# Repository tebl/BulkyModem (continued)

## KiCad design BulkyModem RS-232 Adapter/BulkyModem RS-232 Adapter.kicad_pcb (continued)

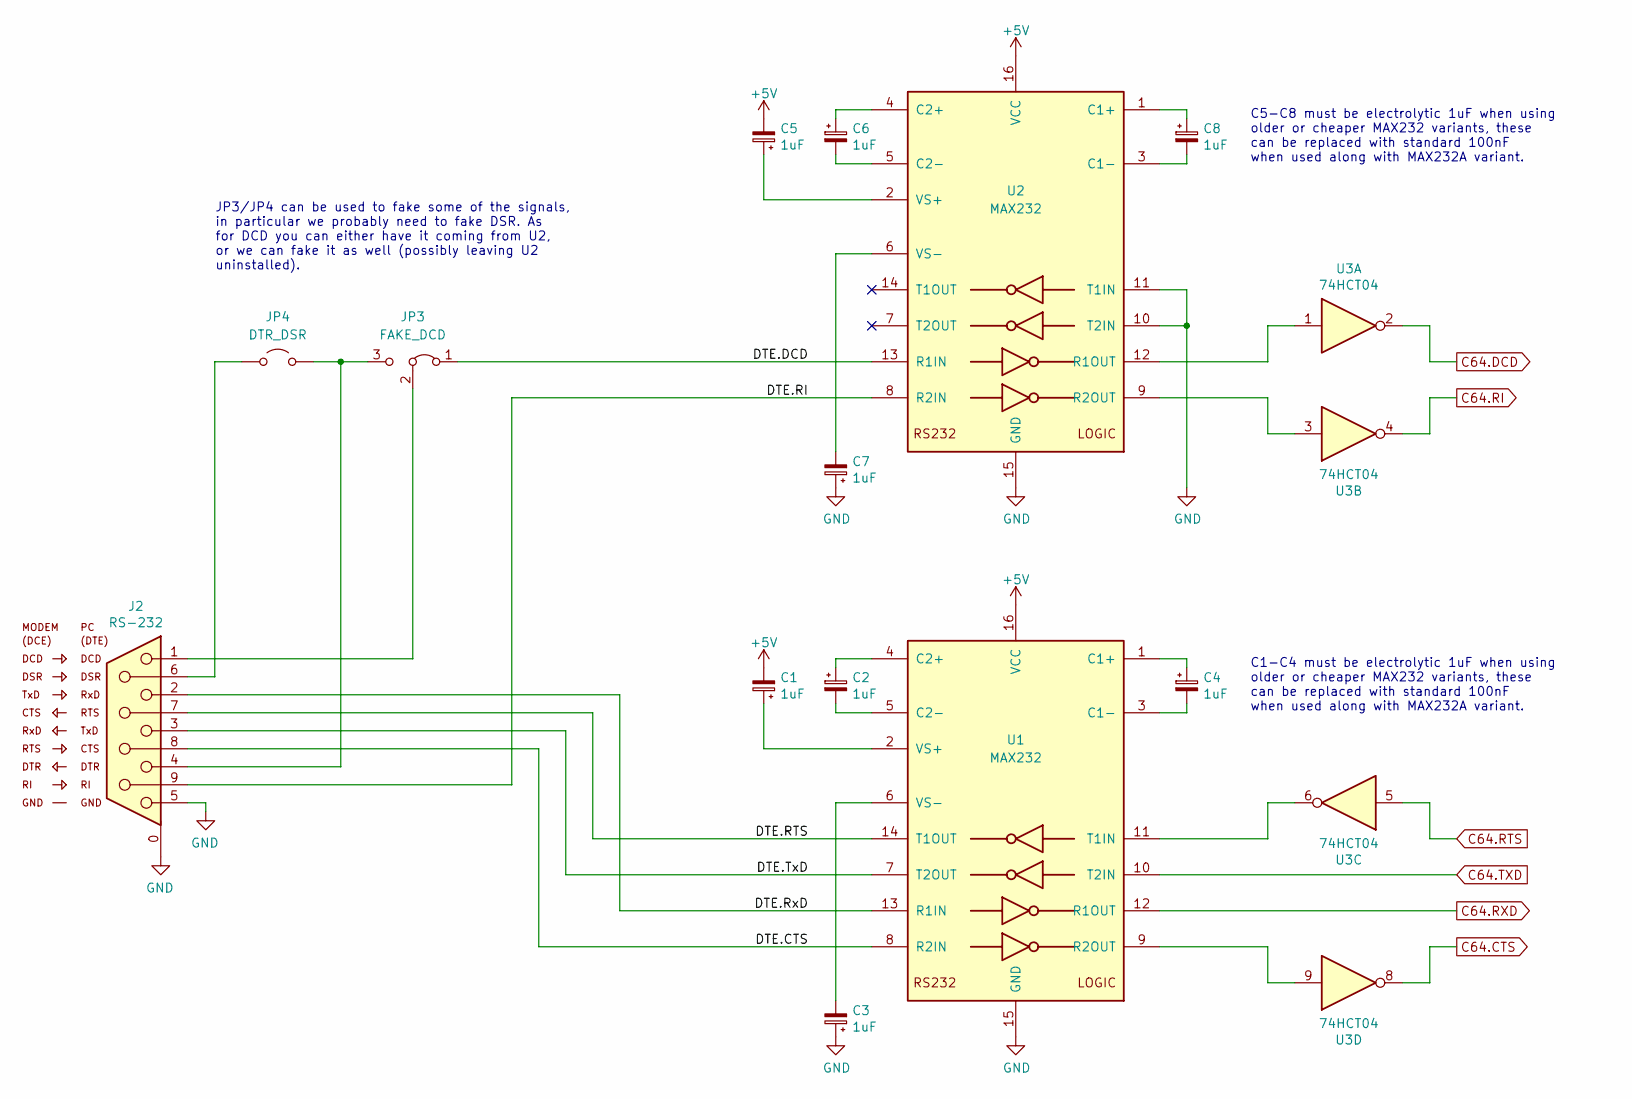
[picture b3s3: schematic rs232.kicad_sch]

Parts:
C1, C2, C3, C4, C5, C6, C7, C8: 1uF; CP_Radial_D4.0mm_P2.00mm_Custom
J2: RS-232; DSUB-9_Male_Horizontal_P2.77x2.84mm_EdgePinOffset7.70mm_Hou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
JP3: FAKE_DCD; PinHeader_1x03_P2.54mm_Vertical
JP4: DTR_DSR; PinHeader_1x02_P2.54mm_Vertical
U1, U2: MAX232; DIP-16_W7.62mm_Socket_LongPads
U3: 74HCT04; DIP-14_W7.62mm_Socket_LongPads

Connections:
+5V: C1.2, C5.2, U1.16 (VCC), U2.16 (VCC); also elsewhere on the board
/RS-232/DTE.CTS: J2.8, U1.8 (R2IN)
/RS-232/DTE.DCD: JP3.1 (A), U2.13 (R1IN)
/RS-232/DTE.RI: J2.9, U2.8 (R2IN)
/RS-232/DTE.RTS: J2.7, U1.14 (T1OUT)
/RS-232/DTE.RxD: J2.2, U1.13 (R1IN)
/RS-232/DTE.TxD: J2.3, U1.7 (T2OUT)
C64.CTS: U3.8; also elsewhere on the board
C64.DCD: U3.2; also elsewhere on the board
C64.RI: U3.4; also elsewhere on the board
C64.RTS: U3.5; also elsewhere on the board
C64.RXD: U1.12 (R1OUT); also elsewhere on the board
C64.TXD: U1.10 (T2IN); also elsewhere on the board
GND: C3.1, C7.1, J2.0 (S), J2.5, U1.15 (GND), U2.10 (T2IN), U2.11 (T1IN), U2.15 (GND); also elsewhere on the board
unnamed: J2.4, JP3.3 (B), JP4.2 (B)
unnamed: J2.1, JP3.2 (C)
unnamed: J2.6, JP4.1 (A)
unnamed: C4.1, U1.1 (C1+)
unnamed: C4.2, U1.3 (C1-)
unnamed: C2.1, U1.4 (C2+)
unnamed: C2.2, U1.5 (C2-)
unnamed: U1.9 (R2OUT), U3.9
unnamed: U1.11 (T1IN), U3.6
unnamed: C1.1, U1.2 (VS+)
unnamed: C3.2, U1.6 (VS-)
unnamed: C8.1, U2.1 (C1+)
unnamed: C8.2, U2.3 (C1-)
unnamed: C6.1, U2.4 (C2+)
unnamed: C6.2, U2.5 (C2-)
unnamed: U2.12 (R1OUT), U3.1
unnamed: U2.9 (R2OUT), U3.3
unnamed: C5.1, U2.2 (VS+)
unnamed: C7.2, U2.6 (VS-)

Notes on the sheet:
C1-C4 must be electrolytic 1uF when using older or cheaper MAX232 variants, these can be replaced with standard 100nF when used along with MAX232A variant.
C5-C8 must be electrolytic 1uF when using older or cheaper MAX232 variants, these can be replaced with standard 100nF when used along with MAX232A variant.
JP3/JP4 can be used to fake some of the signals, in particular we probably need to fake DSR. As for DCD you can either have it coming from U2, or we can fake it as well (possibly leaving U2 uninstalled).

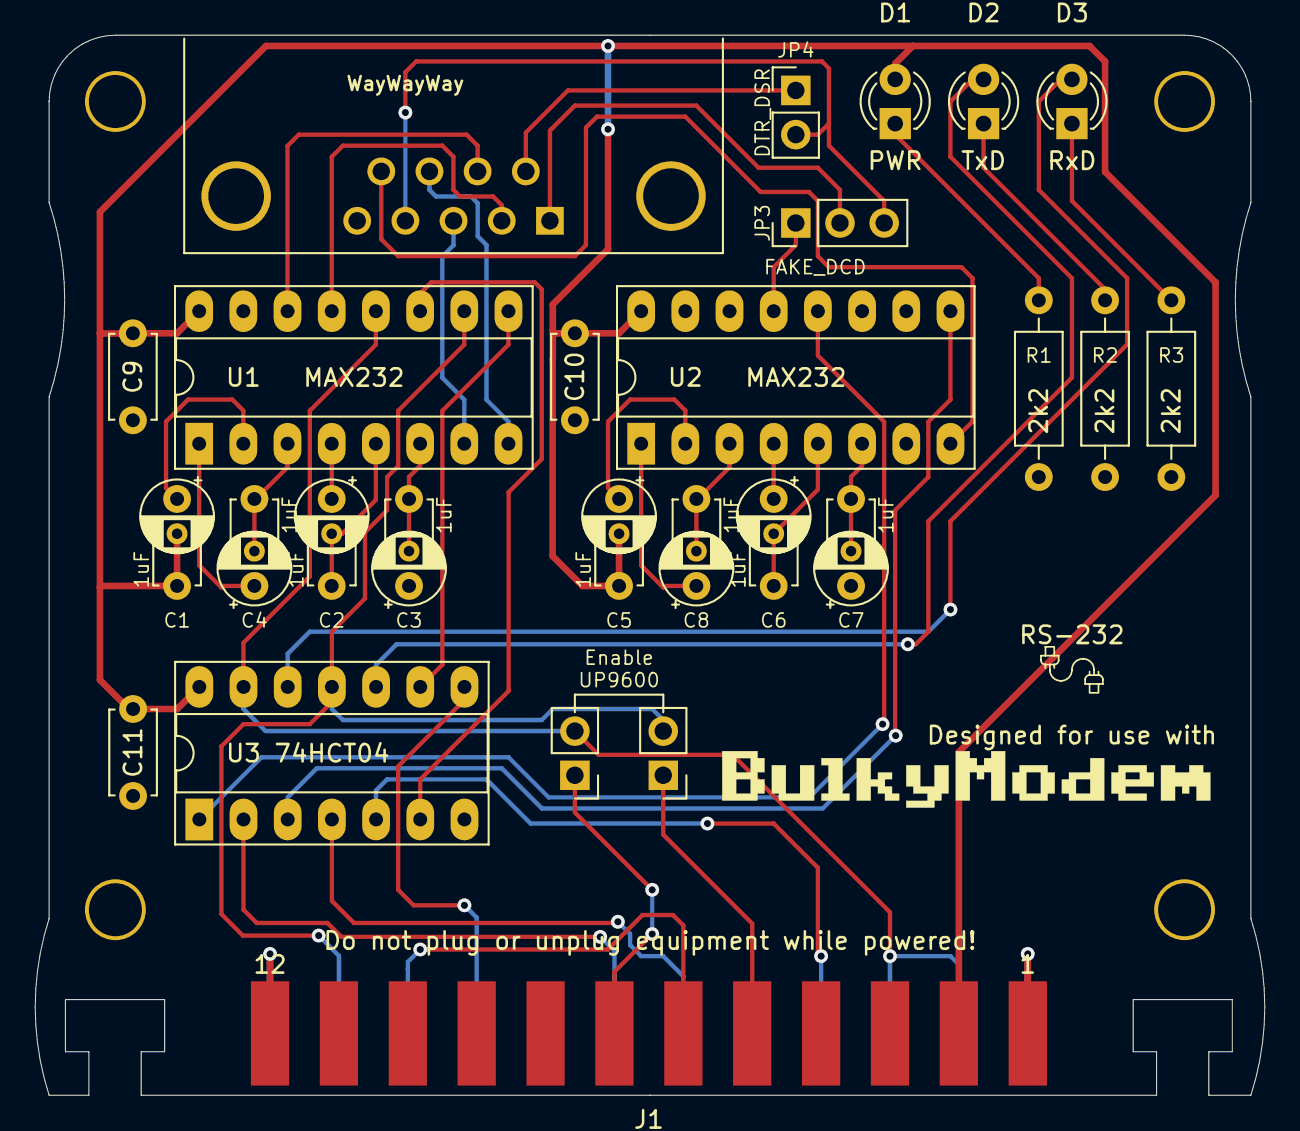
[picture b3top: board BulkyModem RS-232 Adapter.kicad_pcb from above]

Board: 2 copper layers, 70.7 x 60.9 mm, 30 parts (0 on the bottom side), 41 nets.

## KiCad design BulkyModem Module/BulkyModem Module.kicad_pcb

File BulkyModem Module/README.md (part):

# BulkyModem Module
This it it! This is the project that defined this repository! Confusingly having the same name, in a repository that to this date includes several other devices that do the same thing subtly different ways. As all of them, it's a modem for vintage computers. And if you want more details about what this is really about, check out the [root of this repository](https://github.com/tebl/BulkyModem) before continuing.

The *BulkyModem* is based on [Zimodem](https://github.com/bozimmerman/Zimodem), a device that is commonly built in one of two variants: one more general communications device that communicates over RS-232, the second one is a device that connects directly to the *User Port* on a Commodore 64. I don't know about you, but if you were to take a hard look at the things in my basement then you'd find more vintage computers than what my wife probably think that I have (fiercely protected by a rabid dog, claymores etc). Long story short; I have several that fit into either category. So I didn't want to choose one, when I could simply ~~walk into Mordor~~ make one that would be able to work with either. In the hardest way possible by doing it in hardware, at least compared to just forking my own version of the firmware (that would never be able to keep up to date). At its core is your local garden-variety of ESP8266 development boards, sold in all the regular affordable prices as the NodeMCU version 2 or 3.

**NB!** There is also such a thing as the *BulkyModem-32*, where the "32" indicates that it is instead based on common ESP-32 development boards. It has the same features as this one, including a few *extra* ones though nothing that you'd miss if you weren't already aware of their existence. That variant comes with its own set of [documentation](https://github.com/tebl/BulkyModem/tree/main/BulkyModem-32%20Module), and while you're welcome to keep reading below this point - you'll need to read those when building it instead.

- [1> Building the device](#1-building-the-device)
  - [1.1> Soldering it together](#11-soldering-it-together)
  - [1.2> Putting up a front](#12-putting-up-a-front)
  - [1.3> Integrating circuitry](#13-integrating-circuitry)
  - [1.4> Keeping up with the Commodore](#14-keeping-up-with-the-commodore)
  - [1.5> Finishing touches](#15-finishing-touches)
- [2> Schematic](#2-schematic)
- [3> BOM](#3-bom)

# 1> Building the device
Building a device such as this assumes you have at least minor experience soldering things together, my recommendation is that you at the very least have access to a soldering station with a digital temperature adjustment. If such a thing can be considered commercially available where you live, then you should consider starting with 60/40 rosin core solder as the lead-free alternatives tends to be a bit harder to work with.

With requirements for basic equipment sorted, we need to talk a bit about what you want to achieve while building this project. The reason I ask is that while you can build a functional *BulkyModem* using this single PCB by itself, you can also choose to build the complete version of it - including front panels, faceplates and a whole lot of components intended to make it work and look the way I wanted it to. I won't be covering the task of building cheaper or custom versions of it in any great detail, mostly because the concept of the *BulkyModem* is that it shouldn't end up looking like a science experiment. Look into the ["Mini"-variants](https://github.com/tebl/BulkyModem/blob/main/README.md#1-modules) if you just want something that is smaller, or significantly cheaper.

Now that you know have *concepts of a plan* for what you want to build, we can get started on one of the more expensive steps in any build process - shopping! For reference, the most expensive step is probably setting your desk and/or house on fire. Don't be one of those guys! Anyway, when ready to perform the whole shopping thing - head on over to the [BOM](#3-bom)-section for some information on what kind of components that you'll need. While I would have liked to give you specific part numbers for "reputable" electronic part suppliers, I can't afford to shop there. So what I do is to make due with what I can find on sites such as eBay, AliExpress or any other similar sites that seem to sell the same, and quite possibly identical, set of cheap Chinese components. The downside is that I can't link to a part directly and expect it to stay listed tomorrow, so you'll need to consider the description listed more in the category of *suggested search terms* and not *part numbers* in any accurate sense of the definition.

**NB!** Note, however, that the component list found on this page only lists the components required for assembling the main PCB by itself. Those required by the [front panel](https://github.com/tebl/BulkyModem/blob/main/BulkyModem%20Module%20Panel/README.md#3-bom) and [Commodore 64 User Port Adapter](https://github.com/tebl/BulkyModem/blob/main/BulkyModem%20UserPort%20Adapter/README.md#3-bom) are not included in this list, so make sure to browse around.

## 1.1> Soldering it together
Soldering the device together should be a fairly straight-forward affair, just take your time and work your way through the described process before actually attempting to do so. There are some important components that absolutely need to be installed in their correct orientation, and from experience I can tell you that it is significantly easier to do it right in the first place, than it is to desolder and try again.

As mentioned in not so many words, there are options for living without a front panel by skipping out on components components that could be installed on this PCB for the cheaper option. Contrary to what one might first come to assume is that when you want to build the complete version of the *BulkyModem*, then you will want to leave out the positions for 3mm LEDs found at the bottom of your PCB.

I usually recommend starting by having a good look at the PCBs, try to figure out where all of the listed components go and in which orientation they go in (all of this should be clearly marked on the silkscreen). I will usually try to install components in the order of their physical size, meaning that you'll have an easier time trying to keep everything from looking somewhat *wonky*. This is ultimately your board, your build and you want it perfect, don't you? If you said no, then go sit in the corner because I worked hard on creating this for myself and whoever wants to build one.

As for the first step we've actually not installed any components, we've simply taken the step of soldering all of the little solder bridges that are required in order to make it work. While there may be an actual reason for why they're still here, but I didn't want to do a whole revision of the design just to have them hardwired into place. Check out the schematic for what could be considered significantly more informative (the little triangle denotes pin 1), at least beyond explicitly telling you to set them **exactly** like the picture above. While the pads themselves are quite small, they're usually harder to short than you might expect. Just add solder to it then keep dabbing it with your iron until they look right. Measure with a multimeter if you're unsure about the quality of your handiwork.

**NB!** There's a solder bridge on the reverse-side of the PCB, directly below U4. This need to be linked, **only** if you don't intend on installing a chip into the socket. Likewise, a similar solder bridge for bypassing the relay at *K1* also exists though I couldn't possibly imagine not taking the opportunity to install a relay. Because relays are cool!

Here we've started by soldering all of the resistors, ensuring that we're using the correct values in each position. I also forgot one of them, just mentioning that in case you're confused by the apparent cognitive dissonance. R18 isn't an accident, and should not be installed. Considering that you will need to size the value of the resistor going to each of the LEDs, installed either here or on a front panel - then you'll need to do a bit of [math](https://ledcalculator.net/). This is mostly due to the colour and design of the LEDs, but to keep things manageable - all of them will be marked 2k2 and later revisions of the PCB also includes a description of what they are used for. If it just has a value, then install that value. 

Next step is to add a couple of 1N4148 small signal diodes, making sure that the black band of the components matches up with the corresponding markings on your PCB. In the power section there's also a 1N5819 Schottky diode, it looks a bit different though the installation method is the same except that the band on this one is silver or grey. None of it will work if you put those in the wrong way.

Sockets should be installed for the ICs needed for the completed unit. While you could possibly manage without them, they're cheap and you could probably afford to not be quite as *cheap*.  To install I usually solder opposing corners into place, then reheat and push flush against the board before soldering the remaining pins. Note the indent that would indicate *pin 1*, the silkscreen on your PCB should have something similar on that you need to match it up to.

We've also gone ahead and installed our non-polarized capacitors, these have a 5mm pin spacing and could be the old type of ceramic disc capacitors. Or the funky yellow monolithic capacitors as shown, mostly because I prefer the way they look - and the blue ones are on the more expensive side of things (not that I know of any relevant difference between them).

The next step *might* involve a whole lot of the same, populating the four spots below both U3 and U4. If the chips that you've bought to populate those sockets, is the recommended MAX232**A** variant of the chips then these are the same components. If on the other hand, you've received the older *MAX232* (no letter behind name) or the cheaper MAX232**C** variants then you will need to install polarized electrolytic capacitors. There are provisions for both options, but the combination **need** to match up with one another. Polarized means that it should only be installed in the correct orientation, the standard is that you need to match up the stripe on the casing with that of the filled-in white area of your PCB.

At this point I've gone ahead and installed the single LED that I want on the completed unit, as for how it is installed - the longer component lead goes into the round hole and not the square one. If you just had a flashback to some time ago, you either have small kids or an impressive memory! Speaking of memory, I've mentioned earlier that when installing a front panel you don't want to install any LEDs towards the bottom of your PCB.

Then we just need to add some pin headers, mainly those in the upper-right quadrant. As for the female pin headers used for the NodeMCU footprint, we're installing three rows of them to account for the physical differences between commonly available versions of it. While they're somewhat unofficially being referenced to as version 2 and 3, one is physically larger than the other. If you can't find 15-pin female header pins, just find some longer ones and cut them down to size with some judicial application of your pliers. Might look a bit rough, but noone will know unless you explicitly tell people that you're *doing* it. The IDC-socket at the top could be replaced by using standard pin-headers, but it it's there to make it harder for someone to insert the cable the wrong way around.

**NB!** If your development boards don't come with male pin-headers already soldered onto them, use a sacrificial extra PCB to hold the pins straight when soldering them into place. A cheap breadboard is also an option that people seem to recommend, but doing it my way ensures that they're always aligned perfectly!

The right-angle switch added is mostly just duplicating one of the switches found on your development board, so feel free to skip it until I've found out what I was supposed to use it for. For the most part though, it's just a button that's easier to access once the top cover has been installed.

Skipping ahead we've started tinkering with the power section again, mostly by adding the common DC barrel connector (5.5mm x 2.1mm). These are quite notorious for going in crooked so make sure to only solder one pin to get started, then reheat and adjust until perfectly satisfied with your results before soldering in the remaining pins. We've already discussed installing a polarized capacitor, but: white stripe, white area, for mostly no boom! The HK19F-relay (5v variant should be used) has roughly the same indentation as found on the ICs, so you should easily identify the correct orientation. These are notorious for being stuffed into a plastic bag, jammed into an envelope, and then finally being stomped upon with a steel-toed boot - so expect to spend just a little bit of time straightening its legs. 

The *RS-232* side of things requires what's usually labelled as a female right-angle DB9-connector. Say that three times in front of the bathroom mirror in order to have anyone currently living with you, start questioning your sanity. As for the connector itself, this board was designed to fit the component found on sale from Chinese component vendors (most likely a cloned or rebadged version of the RND-branded connectors). As this is specifically the *DCE*-side of a RS-232 communication setup, then the connector should be the female variety for compatibility with *most* vintage computers.

## 1.2> Putting up a front
While actually constructing a suitable front panel is covered in its own entirely separate set of [documentation](https://github.com/tebl/BulkyModem/tree/main/BulkyModem%20Module%20Panel), we should probably cover the process of actually installing it here. However, before we can do all that we need to introduce one of my most used components over the previous decade. Probably resistors now that I actually think about it, but this is the decade of not letting alternative *facts* get in the way of good old-fashioned lies; the component I'm supposed to say something about, is the nylon "hex" standoffs found in each of the corners as shown below. 

For such an innocuous component that should be easy to plop into place, just inserting some nuts on the bottom and be done with it - right? Not so fast there, buddy! You see, I engineered it so that the two at the front needs to be carefully aligned in order to allow the installation of the front panel somewhere beyond this point. It has six sides, and we need to ensure that it is oriented so that it is flush with the left and right outside edges of the PCB. It'll make sense later, I promise!

And through the magic of a text-based time-jump we've skipped the [assembly of the front panel](https://github.com/tebl/BulkyModem/tree/main/BulkyModem%20Module%20Panel). What's currently available on our desk at this point in time, should for the most part appear as can be seen above (ignore faceplate differences as those are mainly just styling). As for the trick with the alignment of the "hex" standoffs as described, both here and when assembling the front panel means that the front panel can slide into place without anything getting in our way. If this still don't make sense, look at the picture below in order to observe how the two should - **eventually** - manage to fit together.

**NB!** While I've just told you to look at this completed assembly, don't forge ahead by soldering anything into place. Not just yet at least!

With the front panel slid into place, the PCBs should slot together quite nicely, and there shouldn't be much of a gap between the two. If you do however find that there's a significant gap, then the likely culprit might be in the production of the PCBs themselves. Not that they're poor, because the fact that we can get a set of PCBs for as low as $2 is simply awe-inspiring - there's simply a limit on how sharp a 90 degree angle can be created when the thing creating the angle is a spinning drill-bit. If this is something you're encountering, then take use a metal file on the corners of the little tabs on the front panel PCB. There are no tracks there so you won't mess anything up, but maybe leave the power tools out of the equation. With that covered, just plop the top cover into place with some temporary standoffs (because they're easy to add and remove by hand). 

Flipping the whole thing over onto its back, we can finally start soldering again. If you've had your soldering iron on for the entire time that you've spent reading my meanderings, then I'm sorry... please accept this free repository full of retro goodness as a way to make it up to you for the apparent loss of power efficiency! With all of my recent ramblings about alignment and so on, you might be worried when doing all of this, but that's exactly the reason why we've already taken precautions to ensure that this won't be an issue by temporarily installing the top faceplate.

And with that, the last of the soldering have been concluded! Any accidental shorts will only show up once you've turned it off, that's just how *The Matrix* has been coded (that's a joke for anyone old/young enough to remember the 90s).

## 1.3> Integrating circuitry
As for adding integrated circuits, mainly just chips of the non-starchy kind, its just a matter of matching up the indentation with that of the sockets that we've hopefully installed sometime earlier. Probably yesterday, but that's just guesswork. A pin straightener will make things easier though a pair of pliers will help you achieve the same thing, just without the same level of visual flair.

And that's all of them installed in their current place. While the chips should be easy to get hold of, the plague of our current no-consequence shopping experience is that a lot of it will be reclaimed or counterfeit chips that will have had a new label printed onto the top of it. Giving inadequately paid people the benefit of doubt, is that the parts will have been roughly sorted into seemingly identical buckets before applying said label. Sometimes that means that completely incompatible technologies have been labelled identically, and we're left to guess why a circuit doesn't work as advertised. If you received a bag of 10, then half of those are more than likely trash. The rest are still a good deal, you just need to swap between them until you find a combination that works (nothing that's considered working should get more than luke-warm to the touch).

As for the brains of the operation, who knows what kind of software have previously been written to it? Probably what we insufferable Arduino-addicts refer to as a "blink"-sketch, but you never know until you actually plug it in. So before you plug it in, make sure to get the applicable [Zimodem](https://github.com/bozimmerman/Zimodem)-firmware onto it before actually plugging it in like shown above. As doing that is a whole other adventure by itself, I've put together my own guide on how anyone with a very particular set of interests can go about actually [setting it up](https://github.com/tebl/BulkyModem/blob/main/documentation/setting_it_up.md). Do that. Then plug it in. Just *don't* do it with any kind of accidental pin-offsets.

## 1.4> Keeping up with the Commodore
Keeping up with the Commodore 64, albeit dragging it kicking and screaming into requirements of the current century requires a suitable adapter. Specifically the one included with this project, helpfully documented with its own entirely different set of [documentation](https://github.com/tebl/BulkyModem/tree/main/BulkyModem%20UserPort%20Adapter) describing its assembly process. It connects to the main body of the *BulkyModem* using commonly available cables, usually labelled as a *16-pin IDC cable* - quite possibly with the word *JTAG* there as well (for some reason). This is what it looks like when in use:

Why is this needed? As the modem is an independently powered device from that of the Commodore 64, we effectively have what can electrically be considered as separate power domains with a cable connecting the two. Except... any connected signal is also a source of power. Leading to somewhat scary issues, such as when a data signal from your C64s crusty old CIA-chip starts attempting to power up the modem - or vice versa. The classic solution to this problem is to only enable communications when both sides can be considered suitably alive, so that's what we're doing here in what's probably a very 1970s way.

## 1.5> Finishing touches

As for finishing touches, it's can be summed up as taking steps towards attaching the top faceplate. Again. But this time you're using *proper* screws. As for where you should go from here, the exciting world of the BBSes is probably one of them. For something more specific, see:

- [Setting it up](https://github.com/tebl/BulkyModem/blob/main/documentation/setting_it_up.md)
- [Getting started](https://github.com/tebl/BulkyModem/blob/main/documentation/getting_started.md)

# 2> Schematic
The supplied KiCad files should be sufficient as both a schematic and as a  starting point for ordering PCBs. Most if not all fabrication companies will expect Gerber-files, these are generated from KiCAD though you will be able to bypass this step by using PCBway shared projects. As for the schematic, one has been provided for you in [PDF-format](https://github.com/tebl/BulkyModem/tree/main/documentation/schematic) - an important source of information when things inevitably fail to work as advertised.

# 3> BOM
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
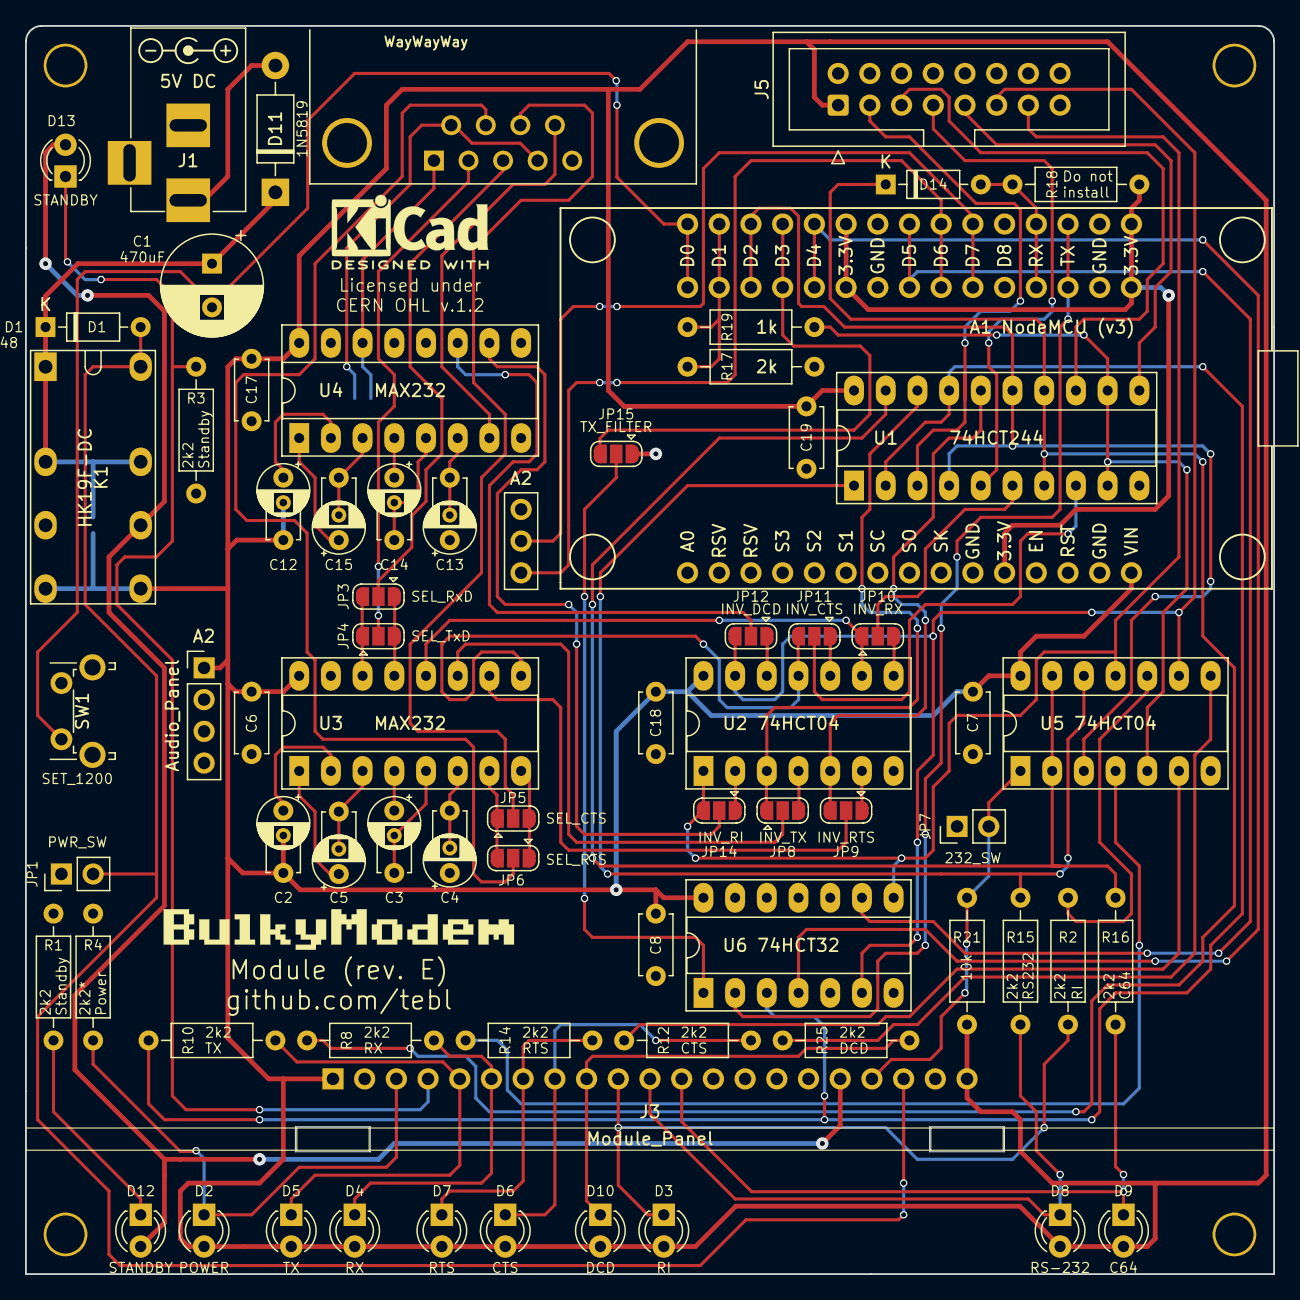
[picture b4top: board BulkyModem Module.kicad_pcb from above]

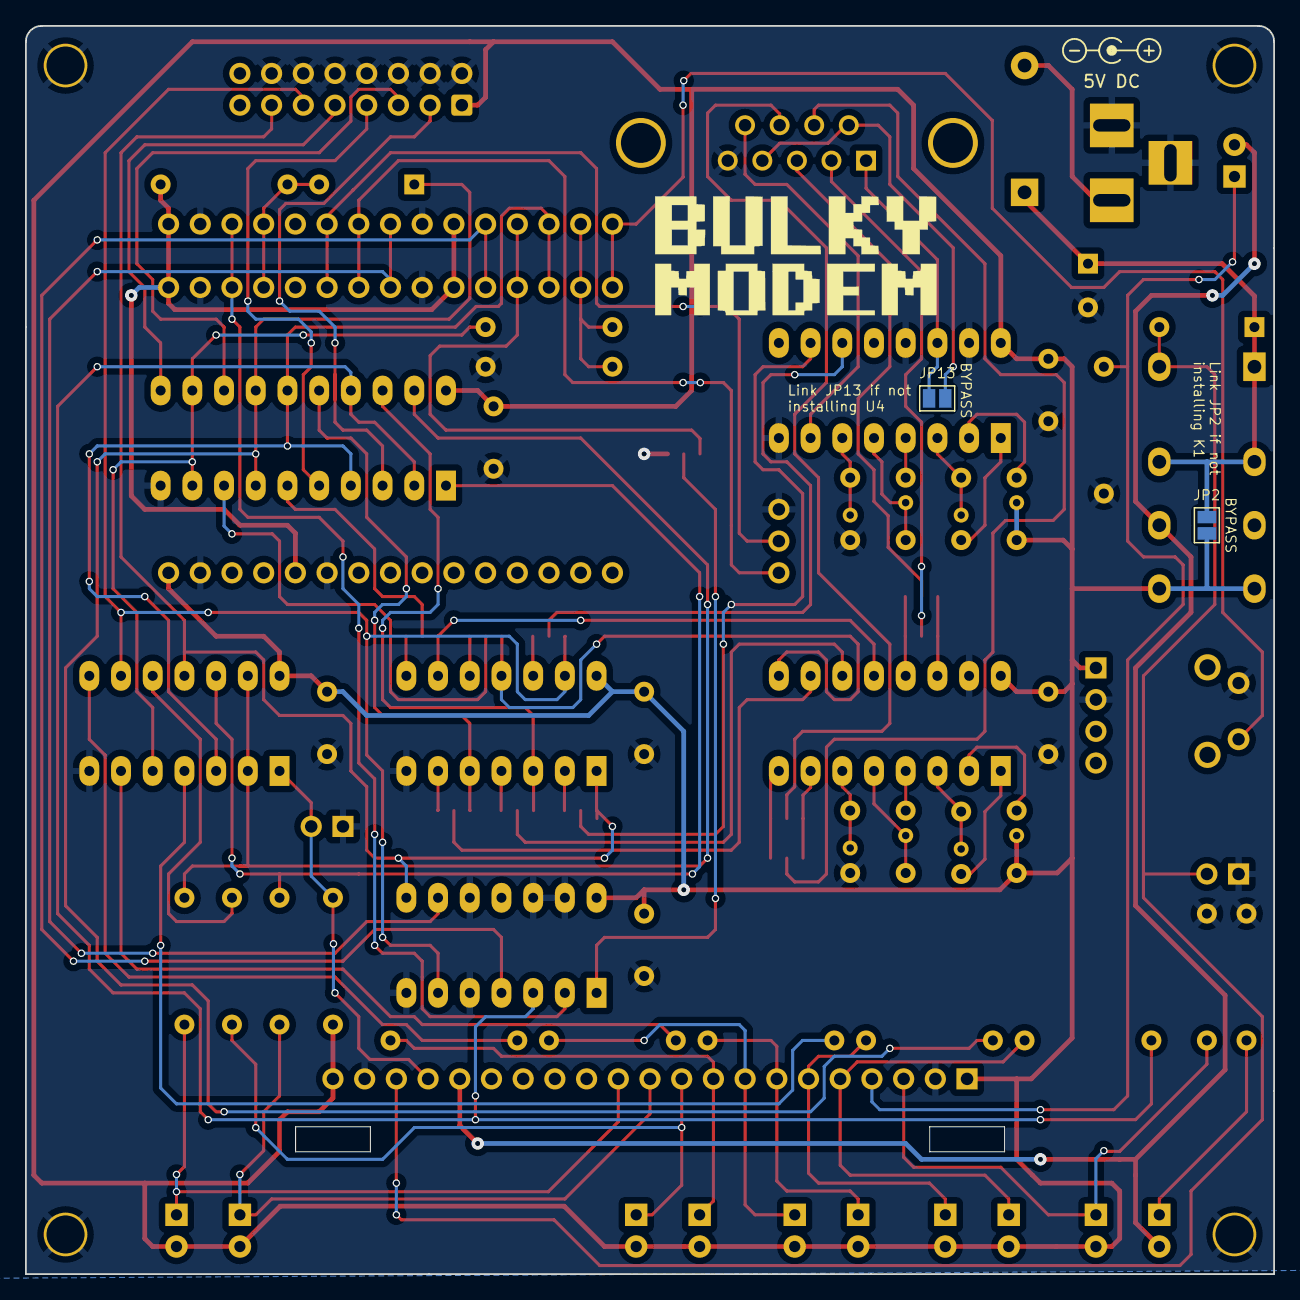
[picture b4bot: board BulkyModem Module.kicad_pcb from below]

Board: 2 copper layers, 100.0 x 100.0 mm, 78 parts (2 on the bottom side), 70 nets.

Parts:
A1: NodeMCU (v3); NodeMCU-LoLinV3
A2: Audio_Panel; AudioModule
C1: 470uF; CP_Radial_D8.0mm_P3.50mm
C2, C3, C4, C5, C12, C13, C14, C15: 1uF; CP_Radial_D4.0mm_P2.00mm_Custom
C6, C7, C8, C17, C18, C19: 100nF; C_Disc_D4.7mm_W2.5mm_P5.00mm
D1: 1n4148; D_DO-35_SOD27_P7.62mm_Horizontal
D2: POWER; LED_D3.0mm
D3: RI; LED_D3.0mm
D4: RX; LED_D3.0mm
D5: TX; LED_D3.0mm
D6: CTS; LED_D3.0mm
D7: RTS; LED_D3.0mm
D8: RS-232; LED_D3.0mm
D9: C64; LED_D3.0mm
D10: DCD; LED_D3.0mm
D11: 1N5819; D_DO-41_SOD81_P10.16mm_Horizontal
D12, D13: STANDBY; LED_D3.0mm
D14: 1N4148; D_DO-35_SOD27_P7.62mm_Horizontal
J1: DC IN; BARREL_JACK
J2: DCE; DSUB-9_Female_Horizontal_P2.77x2.84mm_EdgePinOffset7.70mm_H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
J3: Module_Panel
J5: C64_Modem_OUT; UserPort_Adapter_IDC
JP1: PWR_SW; PinHeader_1x02_P2.54mm_Vertical
JP2, JP13: BYPASS; SolderJumper-2_P1.3mm_Open_Pad1.0x1.5mm
JP3: SEL_RxD; SolderJumper-3_P1.3mm_Open_RoundedPad1.0x1.5mm
JP4: SEL_TxD; SolderJumper-3_P1.3mm_Open_RoundedPad1.0x1.5mm
JP5: SEL_CTS; SolderJumper-3_P1.3mm_Open_RoundedPad1.0x1.5mm
JP6: SEL_RTS; SolderJumper-3_P1.3mm_Open_RoundedPad1.0x1.5mm
JP7: 232_SW; PinHeader_1x02_P2.54mm_Vertical
JP8: INV_TX; SolderJumper-3_P1.3mm_Open_RoundedPad1.0x1.5mm
JP9: INV_RTS; SolderJumper-3_P1.3mm_Open_RoundedPad1.0x1.5mm
JP10: INV_RX; SolderJumper-3_P1.3mm_Open_RoundedPad1.0x1.5mm
JP11: INV_CTS; SolderJumper-3_P1.3mm_Open_RoundedPad1.0x1.5mm
JP12: INV_DCD; SolderJumper-3_P1.3mm_Open_RoundedPad1.0x1.5mm
JP14: INV_RI; SolderJumper-3_P1.3mm_Open_RoundedPad1.0x1.5mm
JP15: TX_FILTER; SolderJumper-3_P1.3mm_Open_RoundedPad1.0x1.5mm
K1: HK19F-DC
M1, M2, M3, M4: Mounting; M3_pin
R1, R2, R3, R8, R10, R12, R14, R15, R16, R25: 2k2; R_Axial_DIN0207_L6.3mm_D2.5mm_P10.16mm_Horizontal
R4: 2k2*; R_Axial_DIN0207_L6.3mm_D2.5mm_P10.16mm_Horizontal
R17: 2k; R_Axial_DIN0207_L6.3mm_D2.5mm_P10.16mm_Horizontal
R18: 10k*; R_Axial_DIN0207_L6.3mm_D2.5mm_P10.16mm_Horizontal
R19: 1k; R_Axial_DIN0207_L6.3mm_D2.5mm_P10.16mm_Horizontal
R21: 10k; R_Axial_DIN0207_L6.3mm_D2.5mm_P10.16mm_Horizontal
SW1: SET_1200; SW_Tactile_SPST_Angled_PTS645Vx39-2LFS
SYM1: DC_5V; PWR_Specification
U1: 74HCT244; DIP-20_W7.62mm_Socket_LongPads
U2, U5: 74HCT04; DIP-14_W7.62mm_Socket_LongPads
U3, U4: MAX232; DIP-16_W7.62mm_Socket_LongPads
U6: 74HCT32; DIP-14_W7.62mm_Socket_LongPads

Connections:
+3.3V: A1.11 (3.3V), A1.16 (3.3V), A1.25 (3.3V), R18.1
+5V: A1.15 (VIN), A2.1 (VCC), C2.2, C6.1, C7.1, C8.1, C12.2, C17.1, C18.1, C19.1, D2.2 (A), D3.2 (A), D4.2 (A), D5.2 (A), D6.2 (A), D7.2 (A), D8.2 (A), D9.2 (A), D10.2 (A), J3.1 (VCC), J3.21 (VCC), J5.1 (VCC), JP2.2 (B), K1.8 (NO_1), K1.9 (NO_2), R21.2, U1.20 (VCC), U2.14 (VCC), U3.16 (VCC), U4.16 (VCC), U5.14 (VCC), U6.14 (VCC)
/232_CTS: JP11.2 (C), U1.8 (1A3)
/232_RTS: JP9.3 (B), U1.16 (1Y1), U2.5
/232_RX: JP10.2 (C), U1.6 (1A2)
/232_TX: JP8.1 (A), U1.18 (1Y0), U2.3
/C64_CTS: J5.5 (CTS), U1.11 (2A3)
/C64_RTS: J5.4 (RTS), U1.5 (2Y1)
/C64_RX: J5.3 (RX), U1.13 (2A2)
/C64_TX: J5.2 (TX), U1.3 (2Y0)
/Front Panel/LED_C64: D9.1 (K), J3.12 (C64), R16.2
/Front Panel/LED_CTS: D6.1 (K), J3.8 (CTS), R12.2
/Front Panel/LED_DCD: D10.1 (K), J3.9 (DCD), R25.2
/Front Panel/LED_POW: D2.1 (K), J3.3 (POW), R4.2
/Front Panel/LED_RI: D3.1 (K), J3.10 (RI), R2.2
/Front Panel/LED_RS232: D8.1 (K), J3.11 (RS-232), R15.2
/Front Panel/LED_RTS: D7.1 (K), J3.7 (RTS), R14.2
/Front Panel/LED_RX: D4.1 (K), J3.6 (RX), R8.2
/Front Panel/LED_STB: D13.1 (K), J3.4 (STB), R3.2
/Front Panel/LED_TX: D5.1 (K), J3.5 (TX), R10.2
/RS-232/DCE_CTS: J2.7, JP5.2 (C)
/RS-232/DCE_RTS: J2.8, JP6.2 (C)
/RS-232/DCE_RxD: J2.3, JP3.2 (C)
/RS-232/DCE_TxD: J2.2, JP4.2 (C)
/RS-232/SER_CTS: JP5.1 (A), JP6.3 (B), U3.8 (R2IN)
/RS-232/SER_DCD: J2.1, JP13.1 (A), U4.14 (T1OUT)
/RS-232/SER_RI: J2.9, U4.7 (T2OUT)
/RS-232/SER_RTS: JP5.3 (B), JP6.1 (A), U3.7 (T2OUT)
/RS-232/SER_RxD: JP3.1 (A), JP4.3 (B), U3.13 (R1IN)
/RS-232/SER_TxD: JP3.3 (B), JP4.1 (A), U3.14 (T1OUT)
/TX_FILTER: A1.27 (D3), JP15.3 (B)
AUDIO_RX: A1.22 (D6), A2.5 (AUDIO_TX)
AUDIO_TX: A1.21 (D7), A2.6 (AUDIO_RX)
ESP_CTS: R19.1, U1.9 (2Y3), U1.12 (1Y3), U5.5
ESP_DCD: J5.6 (DCD), JP12.3 (B), U2.13, U5.9, U6.6
ESP_RI: J5.7 (RI), JP14.3 (B), U2.1, U5.11, U6.8
ESP_RTS: A1.28 (D2), U1.4 (1A1), U1.15 (2A1), U5.3
ESP_RX: D14.1 (K), R8.1, U1.7 (2Y2), U1.14 (1Y2)
ESP_TX: R10.1, U1.2 (1A0), U1.17 (2A0), U6.3
GND: A1.10 (GND), A1.14 (GND), A1.17 (GND), A1.24 (GND), A2.2 (GND), A2.7 (GND), C1.2, C4.1, C6.2, C7.2, C8.2, C13.1, C17.2, C18.2, C19.2, J1.2, J1.3, J2.5, J3.2 (GND), J3.20 (GND), J5.9 (GND), J5.10 (GND), J5.11 (GND), J5.12 (GND), J5.13 (GND), J5.14 (GND), J5.15 (GND), JP1.1 (A), JP7.1 (A), JP15.1 (A), M1.1, M2.1, M3.1, M4.1, R1.1, R3.1, R4.1, R17.1, SW1.2, U1.10 (GND), U2.7 (GND), U3.15 (GND), U4.8 (R2IN), U4.13 (R1IN), U4.15 (GND), U5.7 (GND), U6.5, U6.7 (GND), U6.10, U6.12, U6.13
MODE_232: R15.1, U1.1 (1OE), U5.12
MODE_C64: R16.1, U1.19 (2OE), U5.2, U5.13
MODE_SEL: J3.18 (MODE_SEL), JP7.2 (B), R21.1, U5.1
unnamed: A1.30 (D0), SW1.1
unnamed: A1.29 (D1), R17.2, R19.2
unnamed: A1.26 (D4), U6.4
unnamed: A1.23 (D5), U6.9
unnamed: A1.19 (RX), D14.2 (A), R18.2
unnamed: A1.18 (TX), U6.2
unnamed: D11.2 (A), J1.1
unnamed: D12.1 (K), R1.2
unnamed: JP8.3 (B), U2.4
unnamed: JP8.2 (C), U3.11 (T1IN)
unnamed: JP9.1 (A), U2.6
unnamed: JP9.2 (C), U3.10 (T2IN)
unnamed: JP10.1 (A), U2.9, U3.12 (R1OUT)
unnamed: JP10.3 (B), U2.8
unnamed: JP11.1 (A), U2.10
unnamed: JP11.3 (B), U2.11, U3.9 (R2OUT)
unnamed: JP12.1 (A), U2.12
unnamed: JP12.2 (C), U4.11 (T1IN)
unnamed: J2.4, J2.6, JP13.2 (B)
unnamed: JP14.1 (A), U2.2
unnamed: JP14.2 (C), U4.10 (T2IN)
unnamed: JP15.2 (C), U6.1
unnamed: C12.1, U4.2 (VS+)
unnamed: C13.2, U4.6 (VS-)
PWR_EN: D1.2 (A), J3.19 (PWR_EN), JP1.2 (B), K1.16
VIN: C1.1, D1.1 (K), D11.1 (K), JP2.1 (A), K1.1, K1.4 (COM_1), K1.13 (COM_2)
VSB: D12.2 (A), D13.2 (A), J3.17 (VSB), K1.11 (NC_2)

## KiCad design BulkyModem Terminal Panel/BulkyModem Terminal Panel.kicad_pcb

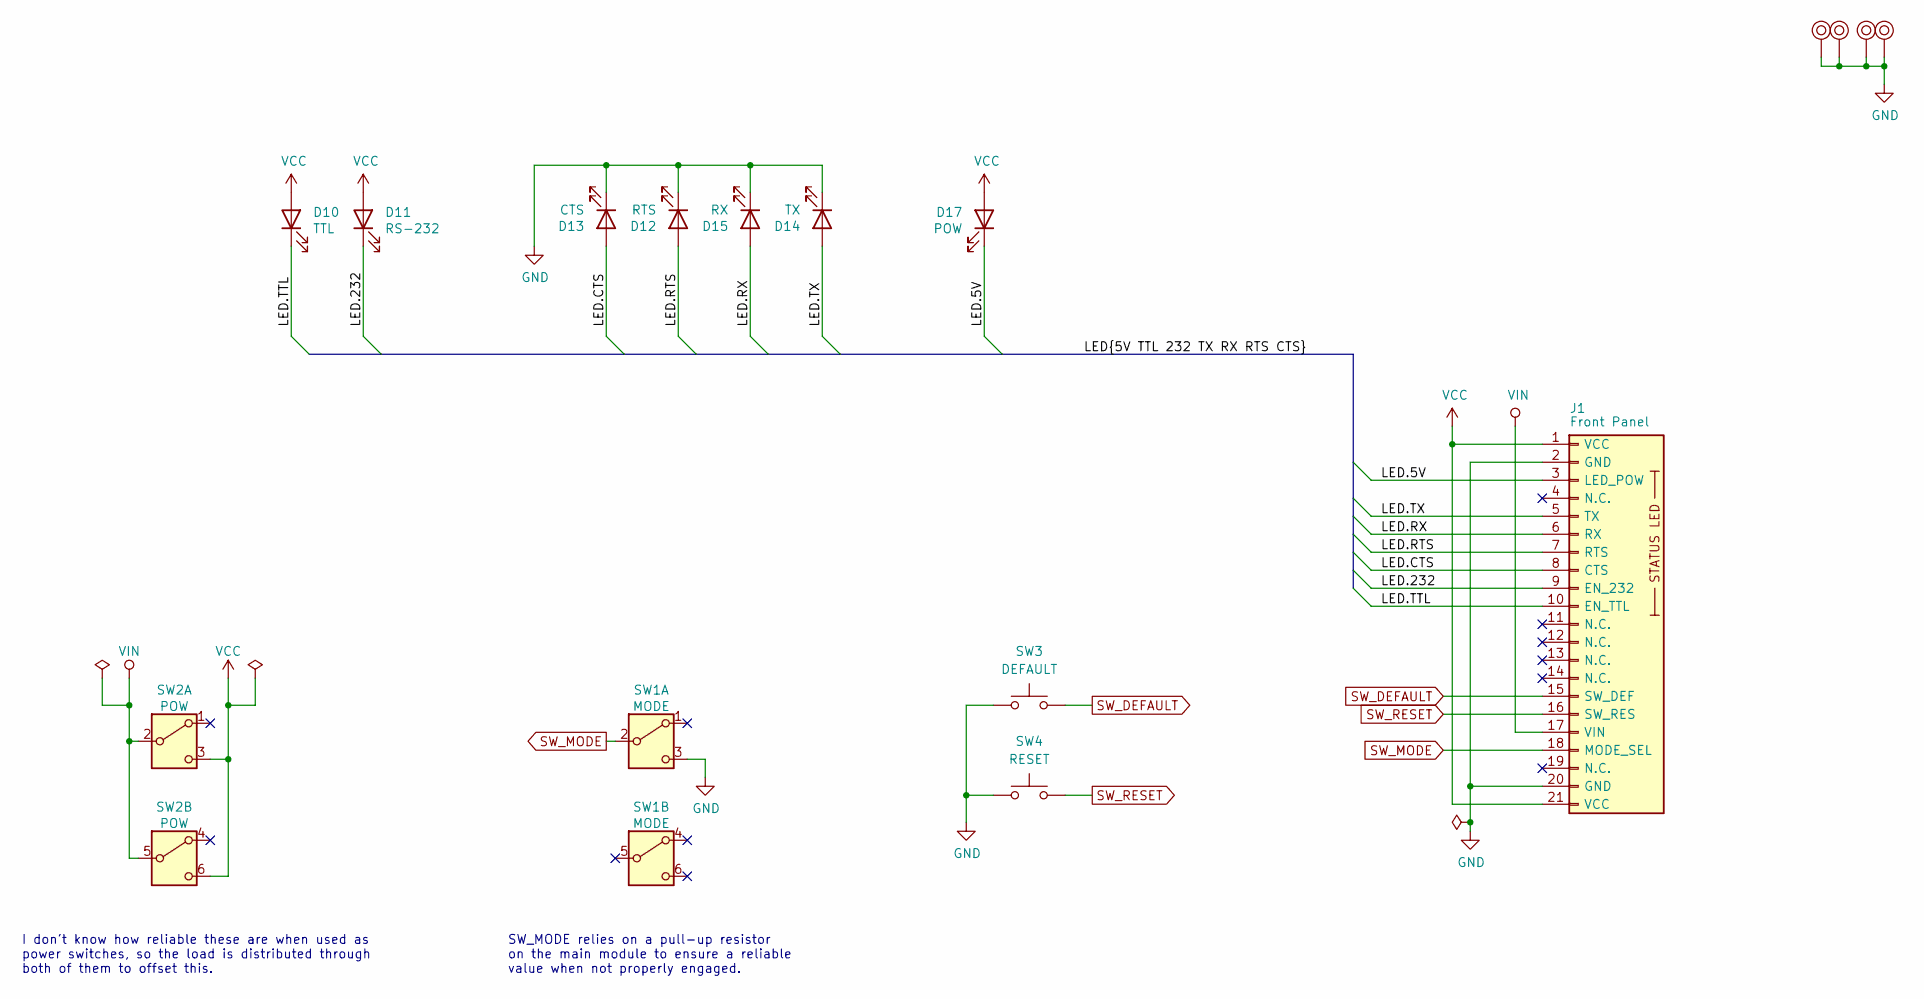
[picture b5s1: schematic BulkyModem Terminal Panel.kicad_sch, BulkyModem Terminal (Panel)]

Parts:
D10: TTL; LED_D5.0mm
D11: RS-232; LED_D5.0mm
D12: RTS; LED_D5.0mm
D13: CTS; LED_D5.0mm
D14: TX; LED_D5.0mm
D15: RX; LED_D5.0mm
D17: POW; LED_D5.0mm
J1: Front Panel; PinHeader_1x21_P2.54mm_Horizontal
M1, M2, M3, M4: Mounting_Pin; M3_pin
SW1: MODE; dpdt_switch_black
SW2: POW; dpdt_switch_black
SW3: DEFAULT; SW_PUSH_6mm
SW4: RESET; SW_PUSH_6mm

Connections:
/LED.5V: D17.1 (K), J1.3 (LED_POW)
/LED.232: D11.1 (K), J1.9 (EN_232)
/LED.CTS: D13.2 (A), J1.8 (CTS)
/LED.RTS: D12.2 (A), J1.7 (RTS)
/LED.RX: D15.2 (A), J1.6 (RX)
/LED.TTL: D10.1 (K), J1.10 (EN_TTL)
/LED.TX: D14.2 (A), J1.5 (TX)
GND: D12.1 (K), D13.1 (K), D14.1 (K), D15.1 (K), J1.2 (GND), J1.20 (GND), M1.1, M2.1, M3.1, M4.1, SW1.3 (C), SW3.1, SW4.1
SW_DEFAULT: J1.15 (SW_DEF), SW3.2
SW_MODE: J1.18 (MODE_SEL), SW1.2 (B)
SW_RESET: J1.16 (SW_RES), SW4.2
VCC: D10.2 (A), D11.2 (A), D17.2 (A), J1.1 (VCC), J1.21 (VCC), SW2.3 (C), SW2.6 (C)
VIN: J1.17 (VIN), SW2.2 (B), SW2.5 (B)

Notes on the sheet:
SW_MODE relies on a pull-up resistor on the main module to ensure a reliable value when not properly engaged.
I don't know how reliable these are when used as power switches, so the load is distributed through both of them to offset this.

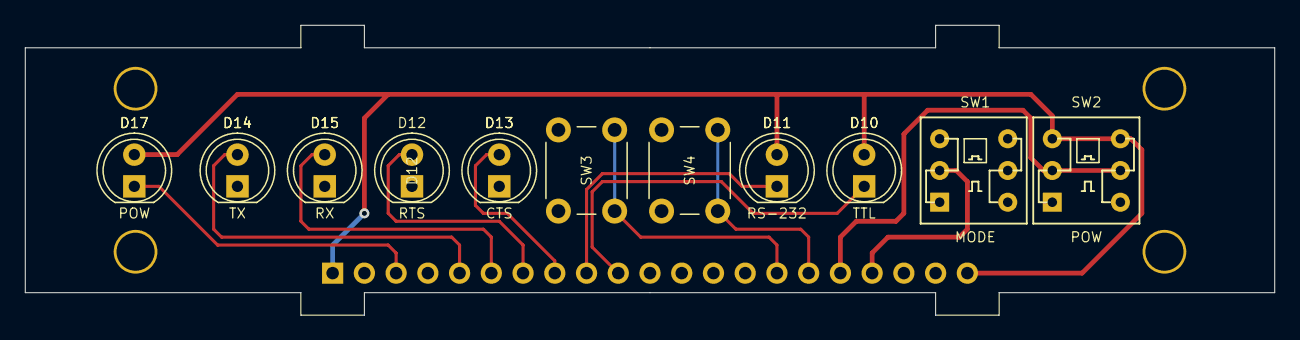
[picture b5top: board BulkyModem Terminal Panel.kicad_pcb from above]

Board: 2 copper layers, 100.0 x 23.2 mm, 16 parts (1 on the bottom side), 13 nets.

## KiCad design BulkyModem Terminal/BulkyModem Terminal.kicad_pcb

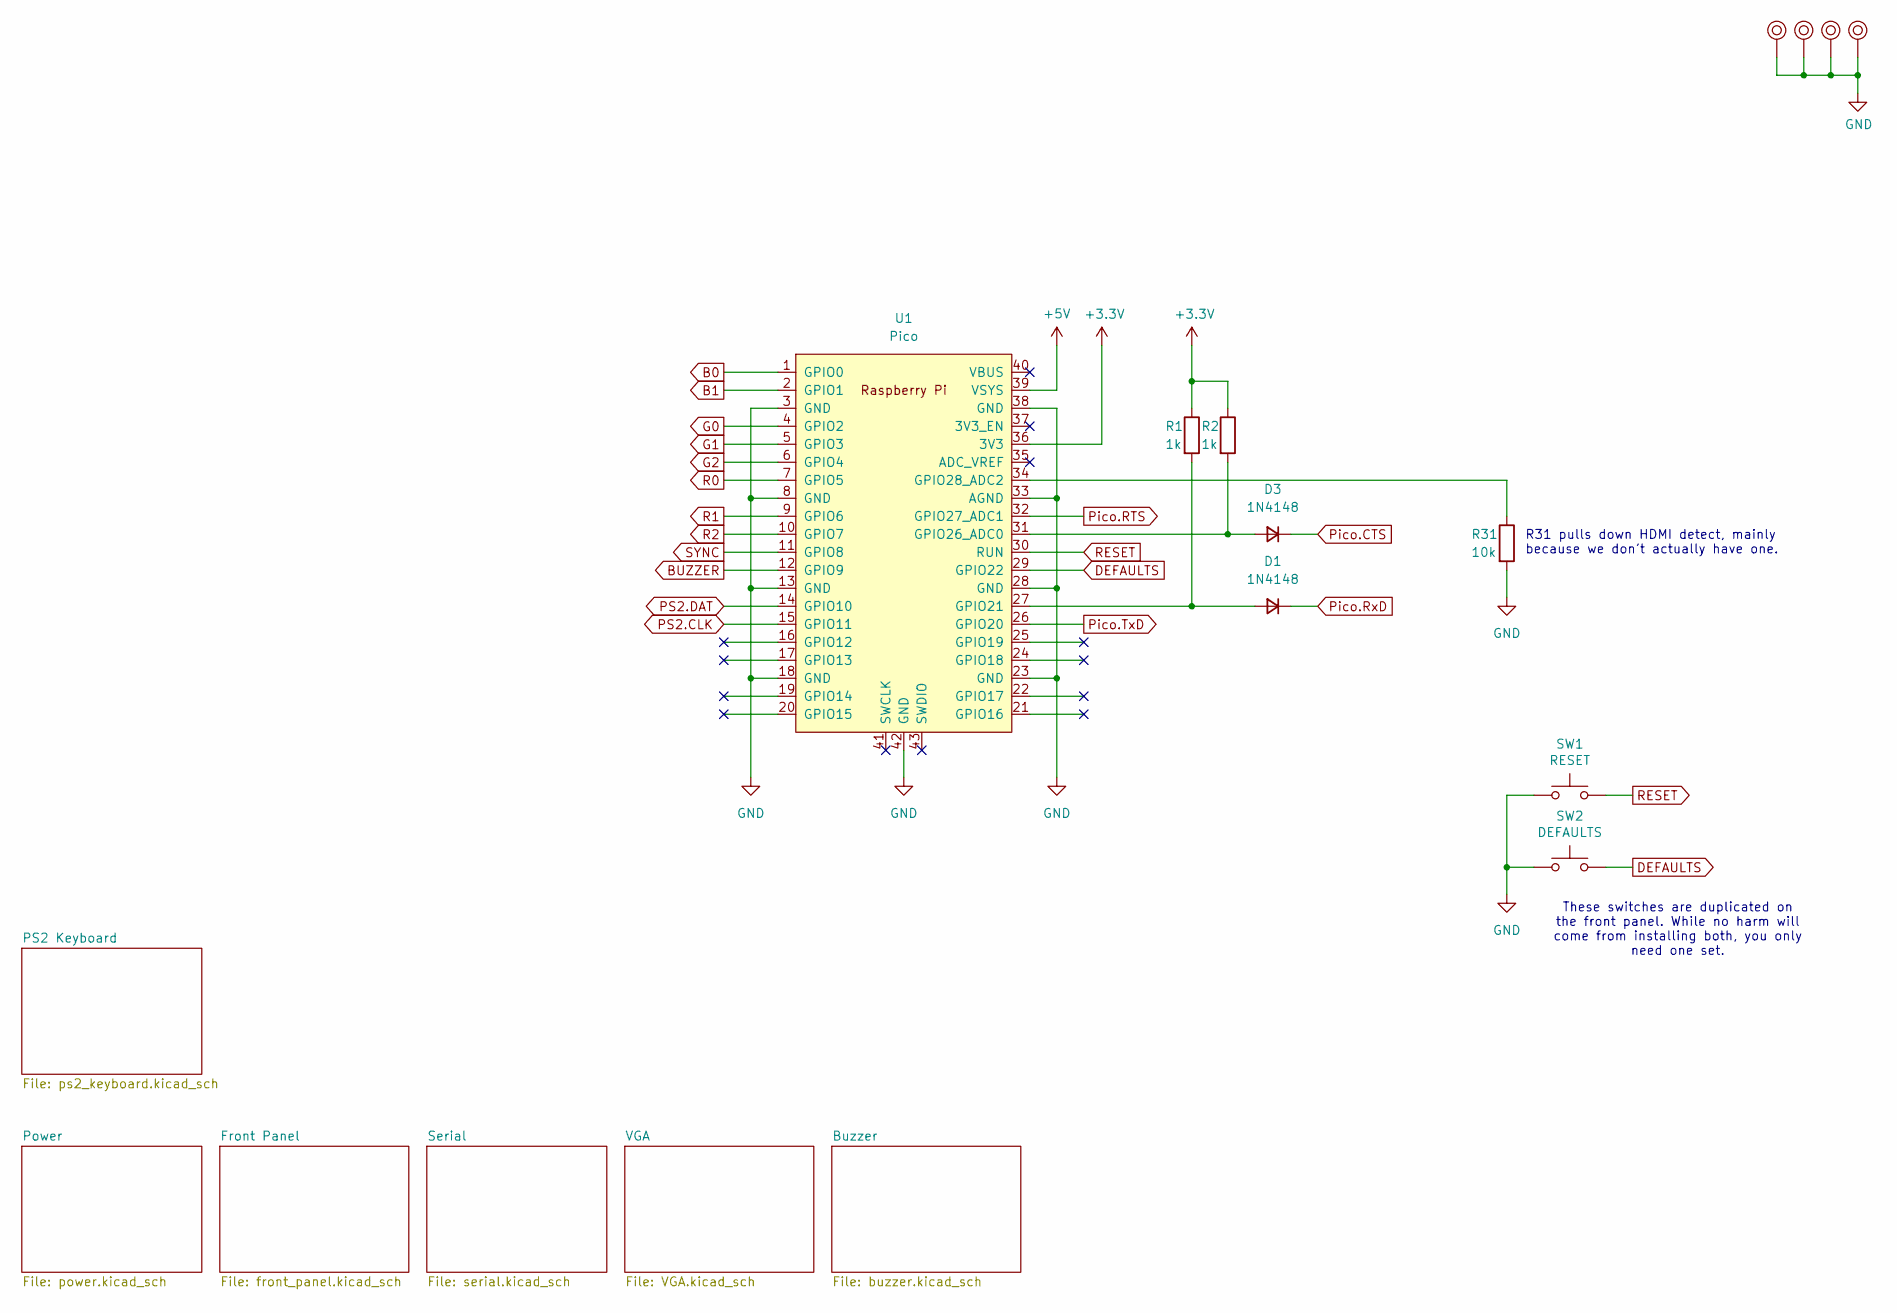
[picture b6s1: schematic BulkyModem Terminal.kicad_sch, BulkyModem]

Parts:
D1, D3: 1N4148; D_DO-35_SOD27_P7.62mm_Horizontal
M1, M2, M3, M4: Mounting; M3_pin
R1, R2: 1k; R_Axial_DIN0207_L6.3mm_D2.5mm_P10.16mm_Horizontal
R31: 10k; R_Axial_DIN0207_L6.3mm_D2.5mm_P10.16mm_Horizontal
SW1: RESET; SW_Tactile_SPST_Angled_PTS645Vx39-2LFS
SW2: DEFAULTS; SW_Tactile_SPST_Angled_PTS645Vx39-2LFS
U1: Pico; RPi_Pico_SMD_TH

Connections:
+3.3V: R1.1, R2.1, U1.36 (3V3); also elsewhere on the board
+5V: U1.39 (VSYS); also elsewhere on the board
B0: U1.1 (GPIO0); also elsewhere on the board
B1: U1.2 (GPIO1); also elsewhere on the board
BUZZER: U1.12 (GPIO9); also elsewhere on the board
DEFAULTS: SW2.2, U1.29 (GPIO22); also elsewhere on the board
G0: U1.4 (GPIO2); also elsewhere on the board
G1: U1.5 (GPIO3); also elsewhere on the board
G2: U1.6 (GPIO4); also elsewhere on the board
GND: M1.1, M2.1, M3.1, M4.1, R31.2, SW1.1, SW2.1, U1.3 (GND), U1.8 (GND), U1.13 (GND), U1.18 (GND), U1.23 (GND), U1.28 (GND), U1.33 (AGND), U1.38 (GND), U1.42 (GND); also elsewhere on the board
unnamed: D1.2 (A), R1.2, U1.27 (GPIO21)
unnamed: D3.2 (A), R2.2, U1.31 (GPIO26_ADC0)
unnamed: R31.1, U1.34 (GPIO28_ADC2)
PS2.CLK: U1.15 (GPIO11); also elsewhere on the board
PS2.DAT: U1.14 (GPIO10); also elsewhere on the board
Pico.CTS: D3.1 (K); also elsewhere on the board
Pico.RTS: U1.32 (GPIO27_ADC1); also elsewhere on the board
Pico.RxD: D1.1 (K); also elsewhere on the board
Pico.TxD: U1.26 (GPIO20); also elsewhere on the board
R0: U1.7 (GPIO5); also elsewhere on the board
R1: U1.9 (GPIO6); also elsewhere on the board
R2: U1.10 (GPIO7); also elsewhere on the board
RESET: SW1.2, U1.30 (RUN); also elsewhere on the board
SYNC: U1.11 (GPIO8); also elsewhere on the board

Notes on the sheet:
These switches are duplicated on the front panel. While no harm will come from installing both, you only need one set.
R31 pulls down HDMI detect, mainly because we don't actually have one.
